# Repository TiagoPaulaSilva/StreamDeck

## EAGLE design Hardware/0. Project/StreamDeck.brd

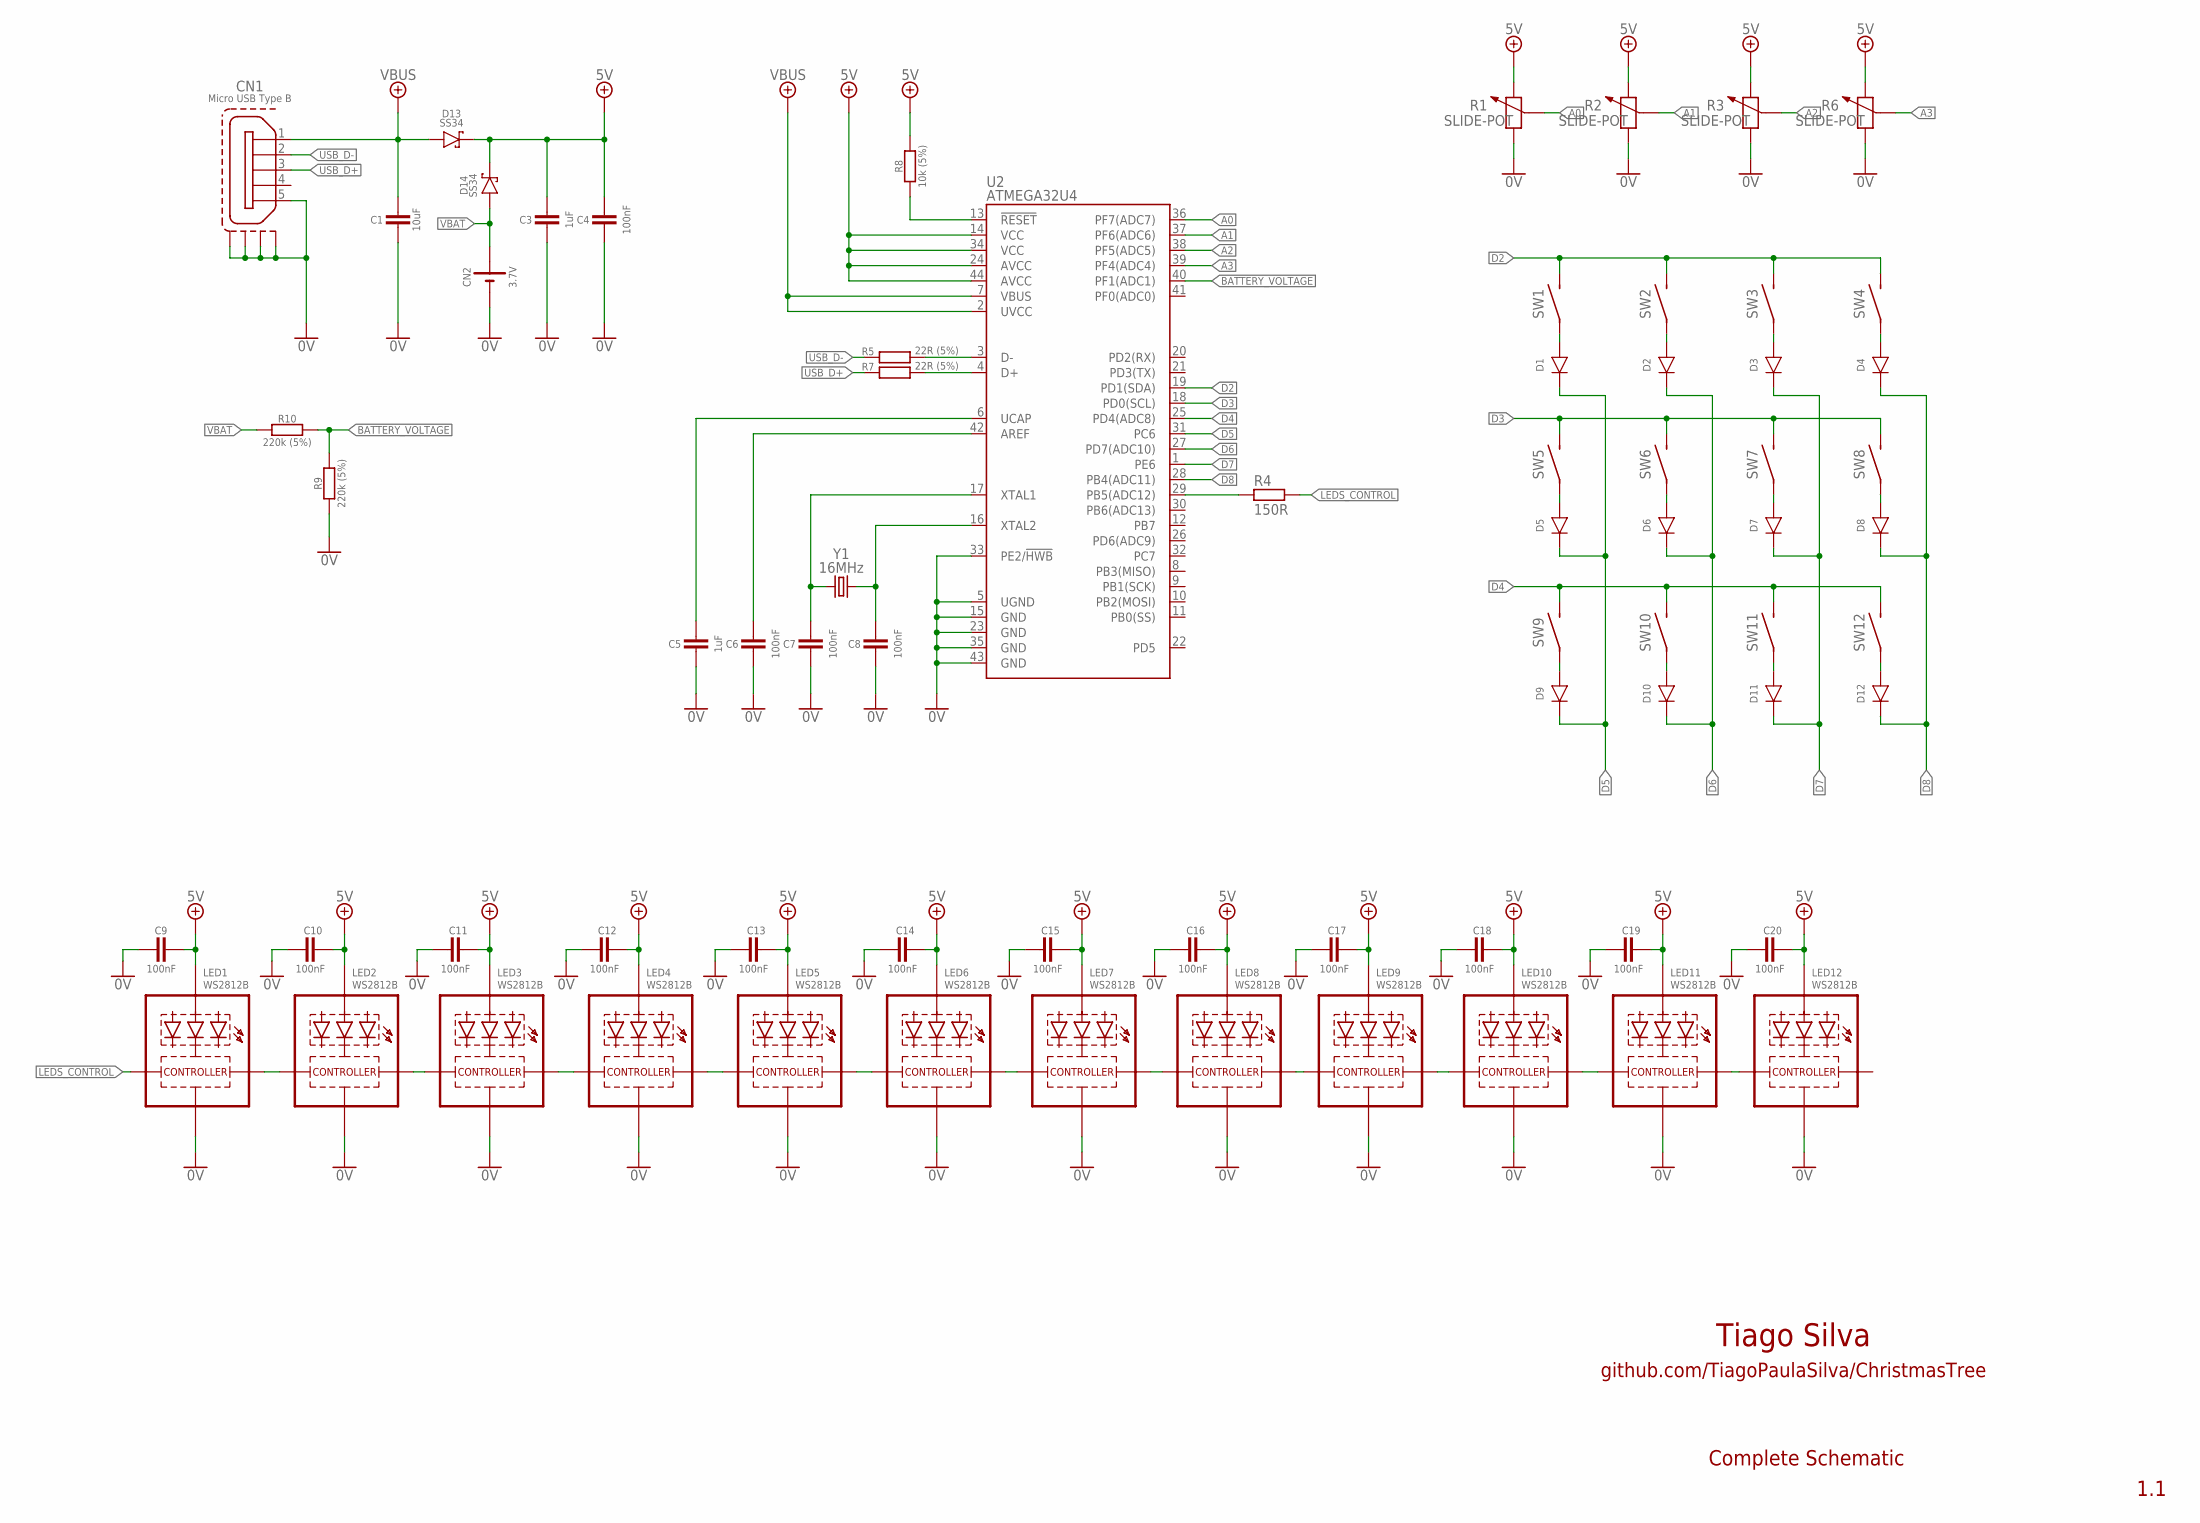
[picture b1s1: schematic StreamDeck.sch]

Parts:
C1: 10uF; C0805
C3, C5: 1uF; C0603
C4, C6, C7, C8, C9, C10, C11, C12, C13, C14, C15, C16, C17, C18, C19, C20: 100nF; C0603
CN1: Micro USB Type B; 10118193-0001LF
CN2: 3.7V; JST-PH2
D1, D2, D3, D4, D5, D6, D7, D8, D9, D10, D11, D12: LL4148; SOD80
D13, D14: SS34; DO214AB
LED1, LED2, LED3, LED4, LED5, LED6, LED7, LED8, LED9, LED10, LED11, LED12: WS2812B; 5050
R1, R2, R3, R6: SLIDE-POT; SLIDER-75MM
R4: 150R; R0603
R5, R7: 22R (5%); R0603
R8: 10k (5%); R0603
R9, R10: 220k (5%); R0603
SW1, SW2, SW3, SW4, SW5, SW6, SW7, SW8, SW9, SW10, SW11, SW12: CHERRY_MX; CHERRY-MX
U2: ATMEGA32U4; TESTING_QFN-44
Y1: 16MHz; 5.0X3.2_KX-9A

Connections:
0V: C1.2, C3.2, C4.2, C5.2, C6.2, C7.2, C8.2, C9.2, C10.2, C11.2, C12.2, C13.2, C14.2, C15.2, C16.2, C17.2, C18.2, C19.2, C20.2, CN1.5, CN1.MP1 (S1), CN1.MP2 (S2), CN1.MP3 (S3), CN1.MP4 (S4), CN2.2 (-), LED1.3-GND (GND), LED2.3-GND (GND), LED3.3-GND (GND), LED4.3-GND (GND), LED5.3-GND (GND), LED6.3-GND (GND), LED7.3-GND (GND), LED8.3-GND (GND), LED9.3-GND (GND), LED10.3-GND (GND), LED11.3-GND (GND), LED12.3-GND (GND), R1.P$1 (1), R2.P$1 (1), R3.P$1 (1), R6.P$1 (1), R9.1, U2.5 (UGND), U2.15 (GND), U2.23 (GND), U2.33 (PE2/!HWB), U2.35 (GND), U2.43 (GND)
5V: C3.1, C4.1, C9.1, C10.1, C11.1, C12.1, C13.1, C14.1, C15.1, C16.1, C17.1, C18.1, C19.1, C20.1, D13.C (K), D14.C (K), LED1.1-VDD (VDD), LED2.1-VDD (VDD), LED3.1-VDD (VDD), LED4.1-VDD (VDD), LED5.1-VDD (VDD), LED6.1-VDD (VDD), LED7.1-VDD (VDD), LED8.1-VDD (VDD), LED9.1-VDD (VDD), LED10.1-VDD (VDD), LED11.1-VDD (VDD), LED12.1-VDD (VDD), R1.P$2 (2), R2.P$2 (2), R3.P$2 (2), R6.P$2 (2), R8.2, U2.14 (VCC), U2.24 (AVCC), U2.34 (VCC), U2.44 (AVCC)
A0: R1.P$6 (3), U2.36 (PF7(ADC7))
A1: R2.P$6 (3), U2.37 (PF6(ADC6))
A2: R3.P$6 (3), U2.38 (PF5(ADC5))
A3: R6.P$6 (3), U2.39 (PF4(ADC4))
BATTERY_VOLTAGE: R9.2, R10.2, U2.40 (PF1(ADC1))
D2: SW1.SW2, SW2.SW2, SW3.SW2, SW4.SW2, U2.19 (PD1(SDA))
D3: SW5.SW2, SW6.SW2, SW7.SW2, SW8.SW2, U2.18 (PD0(SCL))
D4: SW9.SW2, SW10.SW2, SW11.SW2, SW12.SW2, U2.25 (PD4(ADC8))
D5: D1.1 (K), D5.1 (K), D9.1 (K), U2.31 (PC6)
D6: D2.1 (K), D6.1 (K), D10.1 (K), U2.27 (PD7(ADC10))
D7: D3.1 (K), D7.1 (K), D11.1 (K), U2.1 (PE6)
D8: D4.1 (K), D8.1 (K), D12.1 (K), U2.28 (PB4(ADC11))
LEDS_CONTROL: LED1.4-DIN (DI), R4.2
unnamed: D1.2 (A), SW1.SW1
unnamed: D2.2 (A), SW2.SW1
unnamed: D3.2 (A), SW3.SW1
unnamed: D4.2 (A), SW4.SW1
unnamed: LED1.2-DOUT (DO), LED2.4-DIN (DI)
unnamed: D5.2 (A), SW5.SW1
unnamed: D6.2 (A), SW6.SW1
unnamed: D7.2 (A), SW7.SW1
unnamed: D8.2 (A), SW8.SW1
unnamed: LED3.2-DOUT (DO), LED4.4-DIN (DI)
unnamed: D9.2 (A), SW9.SW1
unnamed: D10.2 (A), SW10.SW1
unnamed: D11.2 (A), SW11.SW1
unnamed: D12.2 (A), SW12.SW1
unnamed: LED2.2-DOUT (DO), LED3.4-DIN (DI)
unnamed: LED5.2-DOUT (DO), LED6.4-DIN (DI)
unnamed: LED6.2-DOUT (DO), LED7.4-DIN (DI)
unnamed: LED4.2-DOUT (DO), LED5.4-DIN (DI)
unnamed: LED8.2-DOUT (DO), LED9.4-DIN (DI)
unnamed: LED10.2-DOUT (DO), LED11.4-DIN (DI)
unnamed: LED9.2-DOUT (DO), LED10.4-DIN (DI)
unnamed: LED11.2-DOUT (DO), LED12.4-DIN (DI)
unnamed: LED7.2-DOUT (DO), LED8.4-DIN (DI)
unnamed: C5.1, U2.6 (UCAP)
unnamed: C6.1, U2.42 (AREF)
unnamed: C7.1, U2.17 (XTAL1), Y1.1
unnamed: C8.1, U2.16 (XTAL2), Y1.3 (2)
unnamed: R4.1, U2.29 (PB5(ADC12))
unnamed: R7.2, U2.4 (D+)
unnamed: R5.2, U2.3 (D-)
RESET: R8.1, U2.13 (!RESET)
USB_D+: CN1.3, R7.1
USB_D-: CN1.2, R5.1
VBAT: CN2.1 (+), D14.A, R10.1
VBUS: C1.1, CN1.1, D13.A, U2.2 (UVCC), U2.7 (VBUS)

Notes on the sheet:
Tiago Silva
github.com/TiagoPaulaSilva/ChristmasTree
1.1
Complete Schematic

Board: 2 copper layers, 71 parts (12 on the bottom side), 50 nets, no tracks yet.

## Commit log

2021-03-01 Schematic WIP

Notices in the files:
parts and their libraries:
My-RLC: Copyright (C) 2007, Bob Starr
crystal-geyer_V1_0: Copyright: Geyer-Electronic
